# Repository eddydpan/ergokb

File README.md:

# ergokb
A custom ergo keyboard, fully designed by myself

## design
I had always taken pride in my typing speed. I felt like I can comfortably navigate a computer with the keyboard, and I have been recently growing these skills with KDE Plasma as my DE and vim as my text editor. I had the realization that if I continue typing for the rest of my life, I'd want to make sure I take care of my hands. 

Therefore, I started looking into more ergonomic keyboards. There are plenty of off-the-shelf models--the Sofle, Aurora Corne, and Iris all looked like good options. However, I am a stickler when it comes to price--the absolute worst outcome for me would be buying an expensive off-the-shelf keyboard and it not being a good-fit for my hands that lie on the smaller side. In truth, these keyboards were difficult to vet. With some more research, I came across the [Caldera](https://github.com/christianselig/caldera-keyboard), an open-source keyboard build made by a hobbyist on [YouTube](https://www.youtube.com/watch?v=7UXsD7nSfDY). Aside from the clickbait video title, it was an insightful watch, and it got me interested in learning PCB design. With the price and uncertainties of an off-the-shelf keyboard, I figured I'd rather design my own and put my engineering degree to good use. 

## layout iteration pipeline

In order to test the keyboard geometry custom to my hands, I used Claude Code to build out a pipline to print out the left and right half of the design specified in `ergogen/config.yaml`. After 8 iterations, I landed on a 6-column Colstag split-keyboard with a 4-key thumb cluster. I had to play around with the orientation to ensure everything fits within my reach. This will allow me to map a QWERTY layout as a backup to trying out a more modern and ergonomic layout such as [Gallium](https://layouts.wiki/layouts/2023/gallium/#gallium-colstag).

### pipeline setup guide

```sh
npm --prefix scripts install   # once: ergogen 4.1.0 + pdfkit, pinned (Node tooling lives in scripts/)
```

1. **Edit** `ergogen/config.yaml`. The stagger, splay, and rotation knobs are in its `units:` block.
2. **Visualize**: paste it into [ergogen.xyz](https://ergogen.xyz), or run `npm --prefix scripts run build` for DXFs and the KiCad boards in `output/ergogen/`.
3. **Print sheet**: `npm --prefix scripts run pdf` writes `output/print/ergokb-layout.pdf` (page 1 = left half, page 2 = right, 1:1 scale).
   - Legends come from `keymap.yaml`. Finger rows are written in desk order, left to right; thumbs are keyed by role (`home`, `curl`, `palm`, `extra`).
   - `npm --prefix scripts run pdf -- --layers gallium,qwerty,nav`: the first layer gets the big legend and the others go in the corners (up to 4 layers).
   - `npm --prefix scripts run pdf -- --set ring_stagger=0.5cy --out try.pdf` overrides a tuning knob for one print.
   - `npm --prefix scripts run pdf -- --paper a4`
4. **Print** at 100% / "Actual size" (not "Fit to page"). Check that the 100 mm bar measures 100 mm, then cut along the dashed line.
   The footer records the git commit and every tuning value, so you can tell old prints apart.

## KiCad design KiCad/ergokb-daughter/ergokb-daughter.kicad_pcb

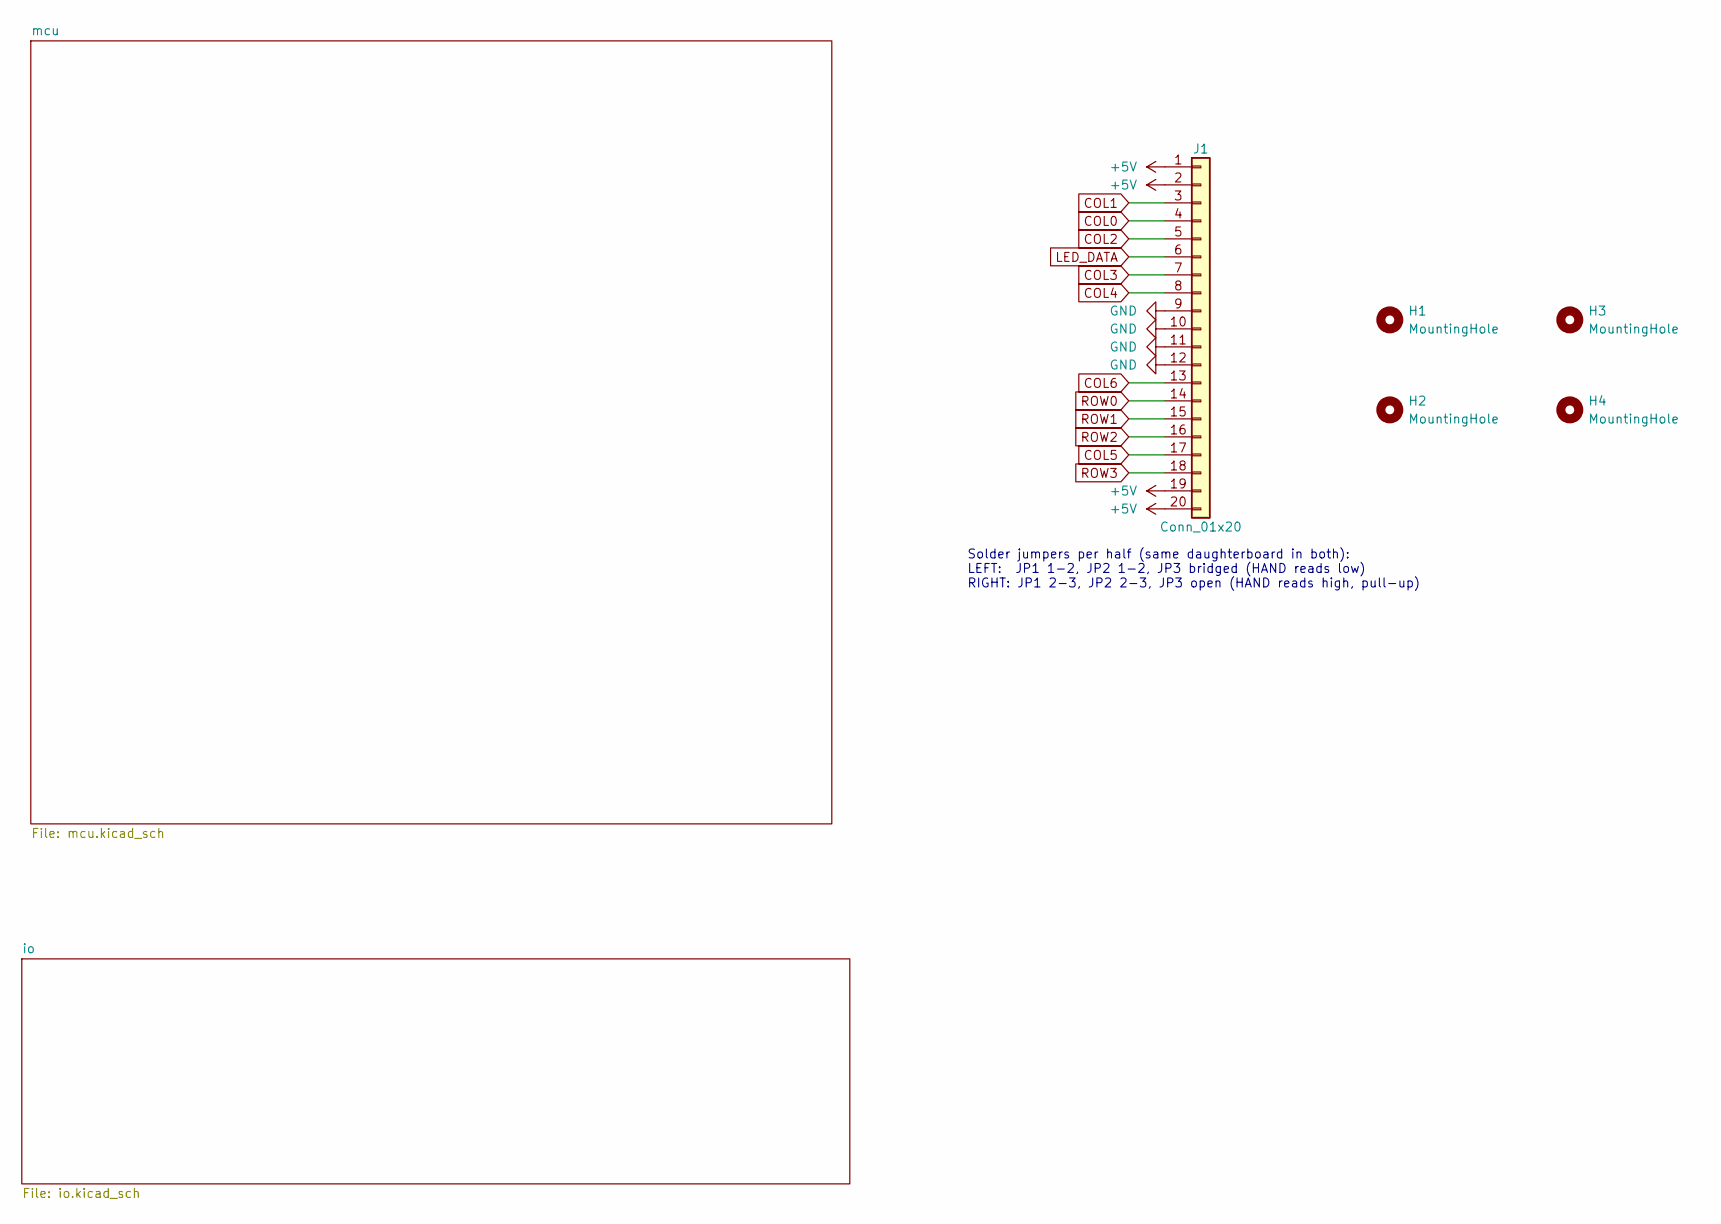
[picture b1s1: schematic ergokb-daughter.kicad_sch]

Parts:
H1, H2, H3, H4: MountingHole; MountingHole_2.2mm_M2
J1: Conn_01x20; PinHeader_1x20_P1.27mm_Vertical

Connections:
+5V: J1.1, J1.2, J1.19, J1.20; also elsewhere on the board
COL0: J1.4; also elsewhere on the board
COL1: J1.3; also elsewhere on the board
COL2: J1.5; also elsewhere on the board
COL3: J1.7; also elsewhere on the board
COL4: J1.8; also elsewhere on the board
COL5: J1.17; also elsewhere on the board
COL6: J1.13; also elsewhere on the board
GND: J1.9, J1.10, J1.11, J1.12; also elsewhere on the board
LED_DATA: J1.6; also elsewhere on the board
ROW0: J1.14; also elsewhere on the board
ROW1: J1.15; also elsewhere on the board
ROW2: J1.16; also elsewhere on the board
ROW3: J1.18; also elsewhere on the board

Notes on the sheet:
Solder jumpers per half (same daughterboard in both): LEFT: JP1 1-2, JP2 1-2, JP3 bridged (HAND reads low) RIGHT: JP1 2-3, JP2 2-3, JP3 open (HAND reads high, pull-up)

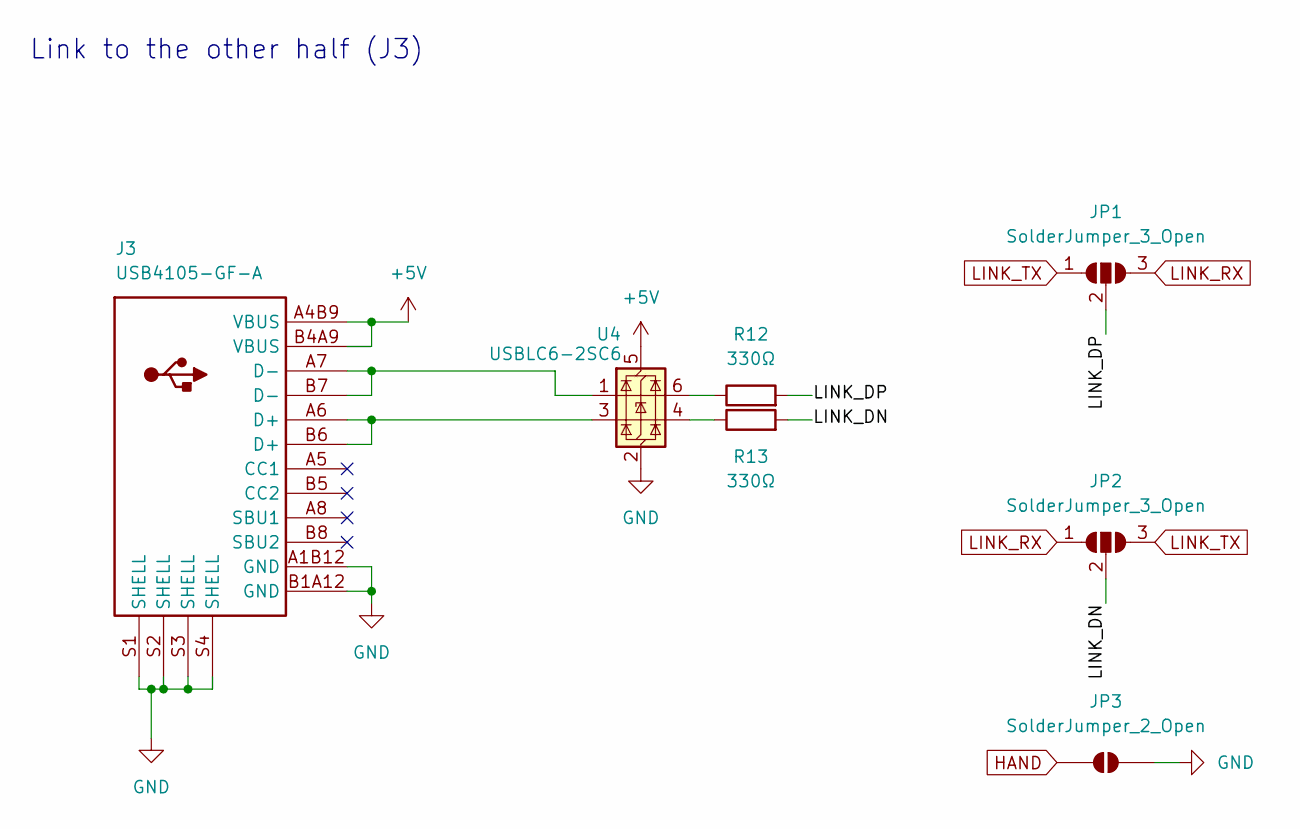
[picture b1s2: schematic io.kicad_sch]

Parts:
J3: USB4105-GF-A
JP1, JP2: SolderJumper_3_Open; SolderJumper-3_P1.3mm_Open_RoundedPad1.0x1.5mm_NumberLabels
JP3: SolderJumper_2_Open; SolderJumper-2_P1.3mm_Open_RoundedPad1.0x1.5mm
R12, R13: 330Ω; R_0603_1608Metric
U4: USBLC6-2SC6; SOT-23-6

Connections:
+5V: J3.A4B9 (VBUS), J3.B4A9 (VBUS), U4.5 (VBUS); also elsewhere on the board
/io/LINK_DN: JP2.2 (C), R13.2
/io/LINK_DP: JP1.2 (C), R12.2
GND: J3.A1B12 (GND), J3.B1A12 (GND), J3.S1 (SHELL), J3.S2 (SHELL), J3.S3 (SHELL), J3.S4 (SHELL), JP3.2 (B), U4.2 (GND); also elsewhere on the board
HAND: JP3.1 (A); also elsewhere on the board
LINK_RX: JP1.3 (B), JP2.1 (A); also elsewhere on the board
LINK_TX: JP1.1 (A), JP2.3 (B); also elsewhere on the board
unnamed: J3.A6 (D+), J3.B6 (D+), U4.3 (I/O2)
unnamed: J3.A7 (D-), J3.B7 (D-), U4.1 (I/O1)
unnamed: R12.1, U4.6 (I/O1)
unnamed: R13.1, U4.4 (I/O2)

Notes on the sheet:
Link to the other half (J3)

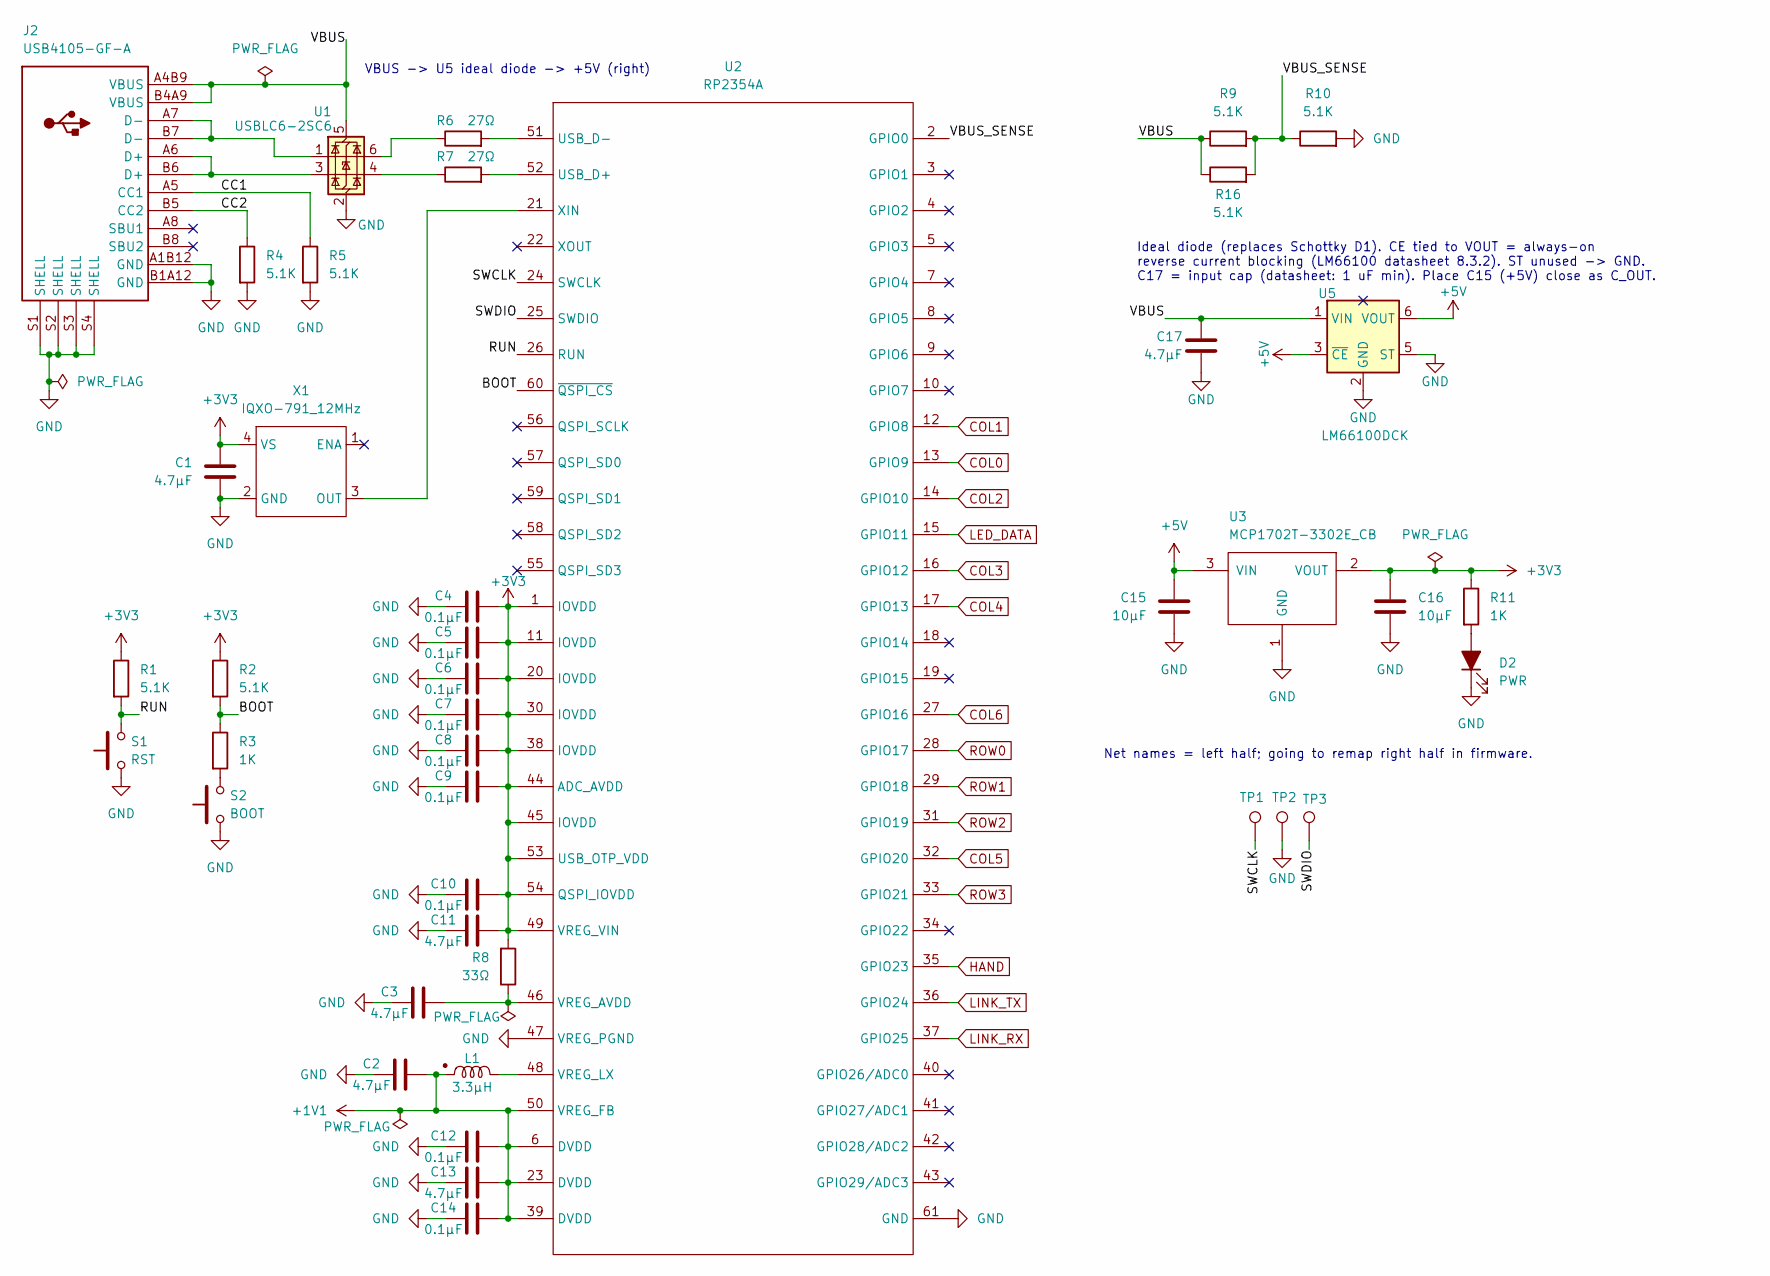
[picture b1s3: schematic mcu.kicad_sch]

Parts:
C1, C13: 4.7µF; C_0402_1005Metric
C2, C11: 4.7µF; R_0402_1005Metric
C3, C17: 4.7µF; C_0603_1608Metric
C4, C5, C12: 0.1µF; C_0603_1608Metric
C6, C7, C8, C9, C10, C14: 0.1µF; C_0402_1005Metric
C15, C16: 10µF; C_0603_1608Metric
D2: PWR; LED_0805_2012Metric
J2: USB4105-GF-A
L1: 3.3µH; AOTA-B201610S3R3-101-T
R1, R2, R9, R10, R16: 5.1K; R_0603_1608Metric
R3: 1K; R_0603_1608Metric
R4, R5: 5.1K; R_0402_1005Metric
R6, R7: 27Ω; R_0402_1005Metric
R8: 33Ω; R_0402_1005Metric
R11: 1K; R_0402_1005Metric
S1: RST; SW_SPST_B3U-1000P
S2: BOOT; SW_SPST_B3U-1000P
TP1, TP2, TP3: TestPoint; TestPoint_Pad_D1.0mm
U1: USBLC6-2SC6; SOT-23-6
U2: RP2354A; RP2350A_QFN-60_EP_7.75x7.75_Pitch0.4mm
U3: MCP1702T-3302E_CB; SOT-23-3
U5: LM66100DCK; SOT-363_SC-70-6
X1: IQXO-791_12MHz; IQXO-791

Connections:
+1V1: C2.2, C12.2, C13.2, C14.2, L1.1, U2.6 (DVDD), U2.23 (DVDD), U2.39 (DVDD), U2.50 (VREG_FB)
+3V3: C1.2, C4.2, C5.2, C6.2, C7.2, C8.2, C9.2, C10.2, C11.2, C16.1, R1.1, R2.1, R8.2, R11.1, U2.1 (IOVDD), U2.11 (IOVDD), U2.20 (IOVDD), U2.30 (IOVDD), U2.38 (IOVDD), U2.44 (ADC_AVDD), U2.45 (IOVDD), U2.49 (VREG_VIN), U2.53 (USB_OTP_VDD), U2.54 (QSPI_IOVDD), U3.2 (VOUT), X1.4 (VS)
+5V: C15.2, U3.3 (VIN), U5.3 (~CE), U5.6 (VOUT); also elsewhere on the board
/mcu/BOOT: R2.2, R3.1, U2.60 (~QSPI_CS)
/mcu/CC1: J2.A5 (CC1), R5.1
/mcu/CC2: J2.B5 (CC2), R4.1
/mcu/RUN: R1.2, S1.2, U2.26 (RUN)
/mcu/SWCLK: TP1.1 (1_1), U2.24 (SWCLK)
/mcu/SWDIO: TP3.1 (1_1), U2.25 (SWDIO)
/mcu/VBUS: C17.1, J2.A4B9 (VBUS), J2.B4A9 (VBUS), R9.1, R16.1, U1.5 (VBUS), U5.1 (VIN)
/mcu/VBUS_SENSE: R9.2, R10.1, R16.2, U2.2 (GPIO0)
COL0: U2.13 (GPIO9); also elsewhere on the board
COL1: U2.12 (GPIO8); also elsewhere on the board
COL2: U2.14 (GPIO10); also elsewhere on the board
COL3: U2.16 (GPIO12); also elsewhere on the board
COL4: U2.17 (GPIO13); also elsewhere on the board
COL5: U2.32 (GPIO20); also elsewhere on the board
COL6: U2.27 (GPIO16); also elsewhere on the board
GND: C1.1, C2.1, C3.1, C4.1, C5.1, C6.1, C7.1, C8.1, C9.1, C10.1, C11.1, C12.1, C13.1, C14.1, C15.1, C16.2, C17.2, D2.1 (K), J2.A1B12 (GND), J2.B1A12 (GND), J2.S1 (SHELL), J2.S2 (SHELL), J2.S3 (SHELL), J2.S4 (SHELL), R4.2, R5.2, R10.2, S1.1, S2.1, TP2.1 (1_1), U1.2 (GND), U2.47 (VREG_PGND), U2.61 (GND), U3.1 (GND), U5.2 (GND), U5.5 (ST), X1.2 (GND); also elsewhere on the board
HAND: U2.35 (GPIO23); also elsewhere on the board
LED_DATA: U2.15 (GPIO11); also elsewhere on the board
LINK_RX: U2.37 (GPIO25); also elsewhere on the board
LINK_TX: U2.36 (GPIO24); also elsewhere on the board
unnamed: D2.2 (A), R11.2
unnamed: J2.A6 (D+), J2.B6 (D+), U1.3 (I/O2)
unnamed: J2.A7 (D-), J2.B7 (D-), U1.1 (I/O1)
unnamed: R3.2, S2.2
unnamed: R6.1, U1.6 (I/O1)
unnamed: R7.1, U1.4 (I/O2)
unnamed: R7.2, U2.52 (USB_D+)
unnamed: R6.2, U2.51 (USB_D-)
unnamed: C3.2, R8.1, U2.46 (VREG_AVDD)
unnamed: L1.2, U2.48 (VREG_LX)
unnamed: U2.21 (XIN), X1.3 (OUT)
ROW0: U2.28 (GPIO17); also elsewhere on the board
ROW1: U2.29 (GPIO18); also elsewhere on the board
ROW2: U2.31 (GPIO19); also elsewhere on the board
ROW3: U2.33 (GPIO21); also elsewhere on the board

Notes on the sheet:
Ideal diode (replaces Schottky D1). CE tied to VOUT = always-on reverse current blocking (LM66100 datasheet 8.3.2). ST unused -> GND. C17 = input cap (datasheet: 1 uF min). Place C15 (+5V) close as C_OUT.
VBUS -> U5 ideal diode -> +5V (right)
Net names = left half; going to remap right half in firmware.

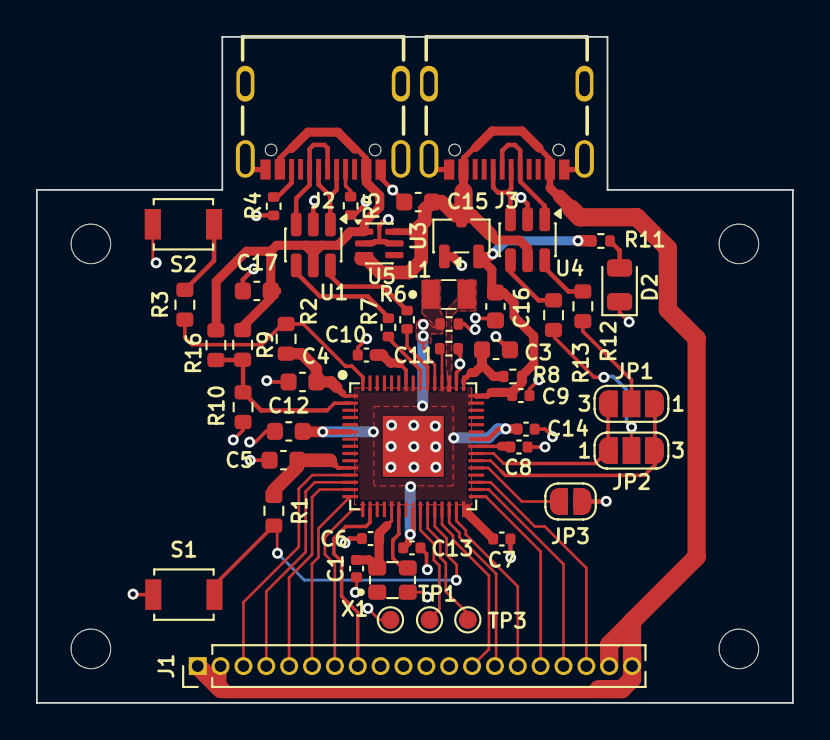
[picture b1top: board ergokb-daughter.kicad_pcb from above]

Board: 2 copper layers, 42.0 x 37.0 mm, 54 parts (0 on the bottom side), 44 nets.

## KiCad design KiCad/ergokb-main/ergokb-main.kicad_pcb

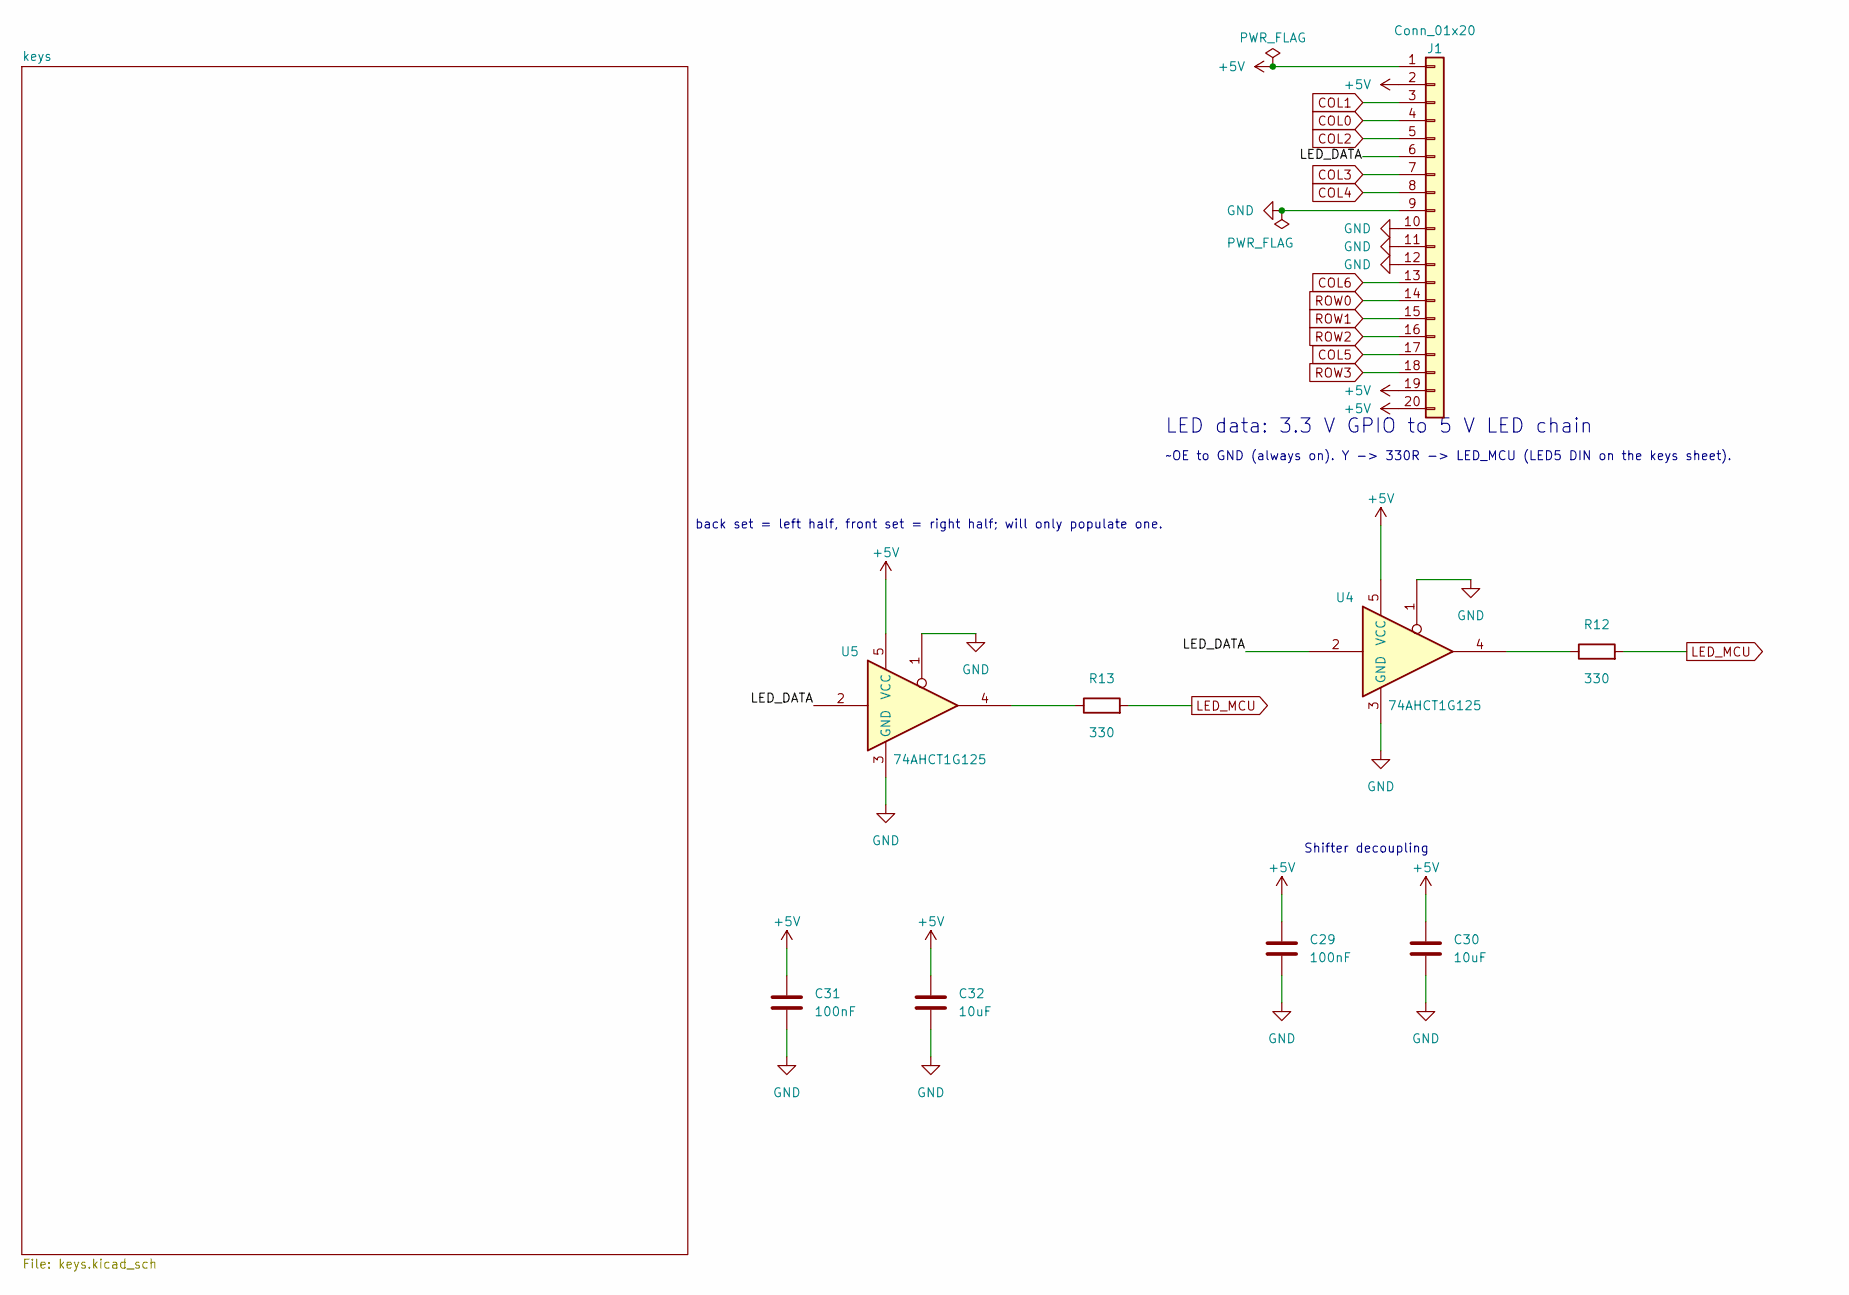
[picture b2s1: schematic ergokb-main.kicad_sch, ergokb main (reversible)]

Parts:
C29, C31: 100nF; C_0603_1608Metric
C30, C32: 10uF; C_0603_1608Metric
J1: Conn_01x20; PinHeader_1x20_P1.27mm_Vertical
R12, R13: 330; R_0603_1608Metric
U4, U5: 74AHCT1G125; SOT-23-5

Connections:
+5V: C29.1, C30.1, C31.1, C32.1, J1.1, J1.2, J1.19, J1.20, U4.5 (VCC), U5.5 (VCC); also elsewhere on the board
/LED_DATA: J1.6, U4.2, U5.2
COL0: J1.4; also elsewhere on the board
COL1: J1.3; also elsewhere on the board
COL2: J1.5; also elsewhere on the board
COL3: J1.7; also elsewhere on the board
COL4: J1.8; also elsewhere on the board
COL5: J1.17; also elsewhere on the board
COL6: J1.13; also elsewhere on the board
GND: C29.2, C30.2, C31.2, C32.2, J1.9, J1.10, J1.11, J1.12, U4.1, U4.3 (GND), U5.1, U5.3 (GND); also elsewhere on the board
LED_MCU: R12.2, R13.2; also elsewhere on the board
unnamed: R12.1, U4.4
unnamed: R13.1, U5.4
ROW0: J1.14; also elsewhere on the board
ROW1: J1.15; also elsewhere on the board
ROW2: J1.16; also elsewhere on the board
ROW3: J1.18; also elsewhere on the board

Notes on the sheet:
back set = left half, front set = right half; will only populate one.
Shifter decoupling
LED data: 3.3 V GPIO to 5 V LED chain
~OE to GND (always on). Y -> 330R -> LED_MCU (LED5 DIN on the keys sheet).

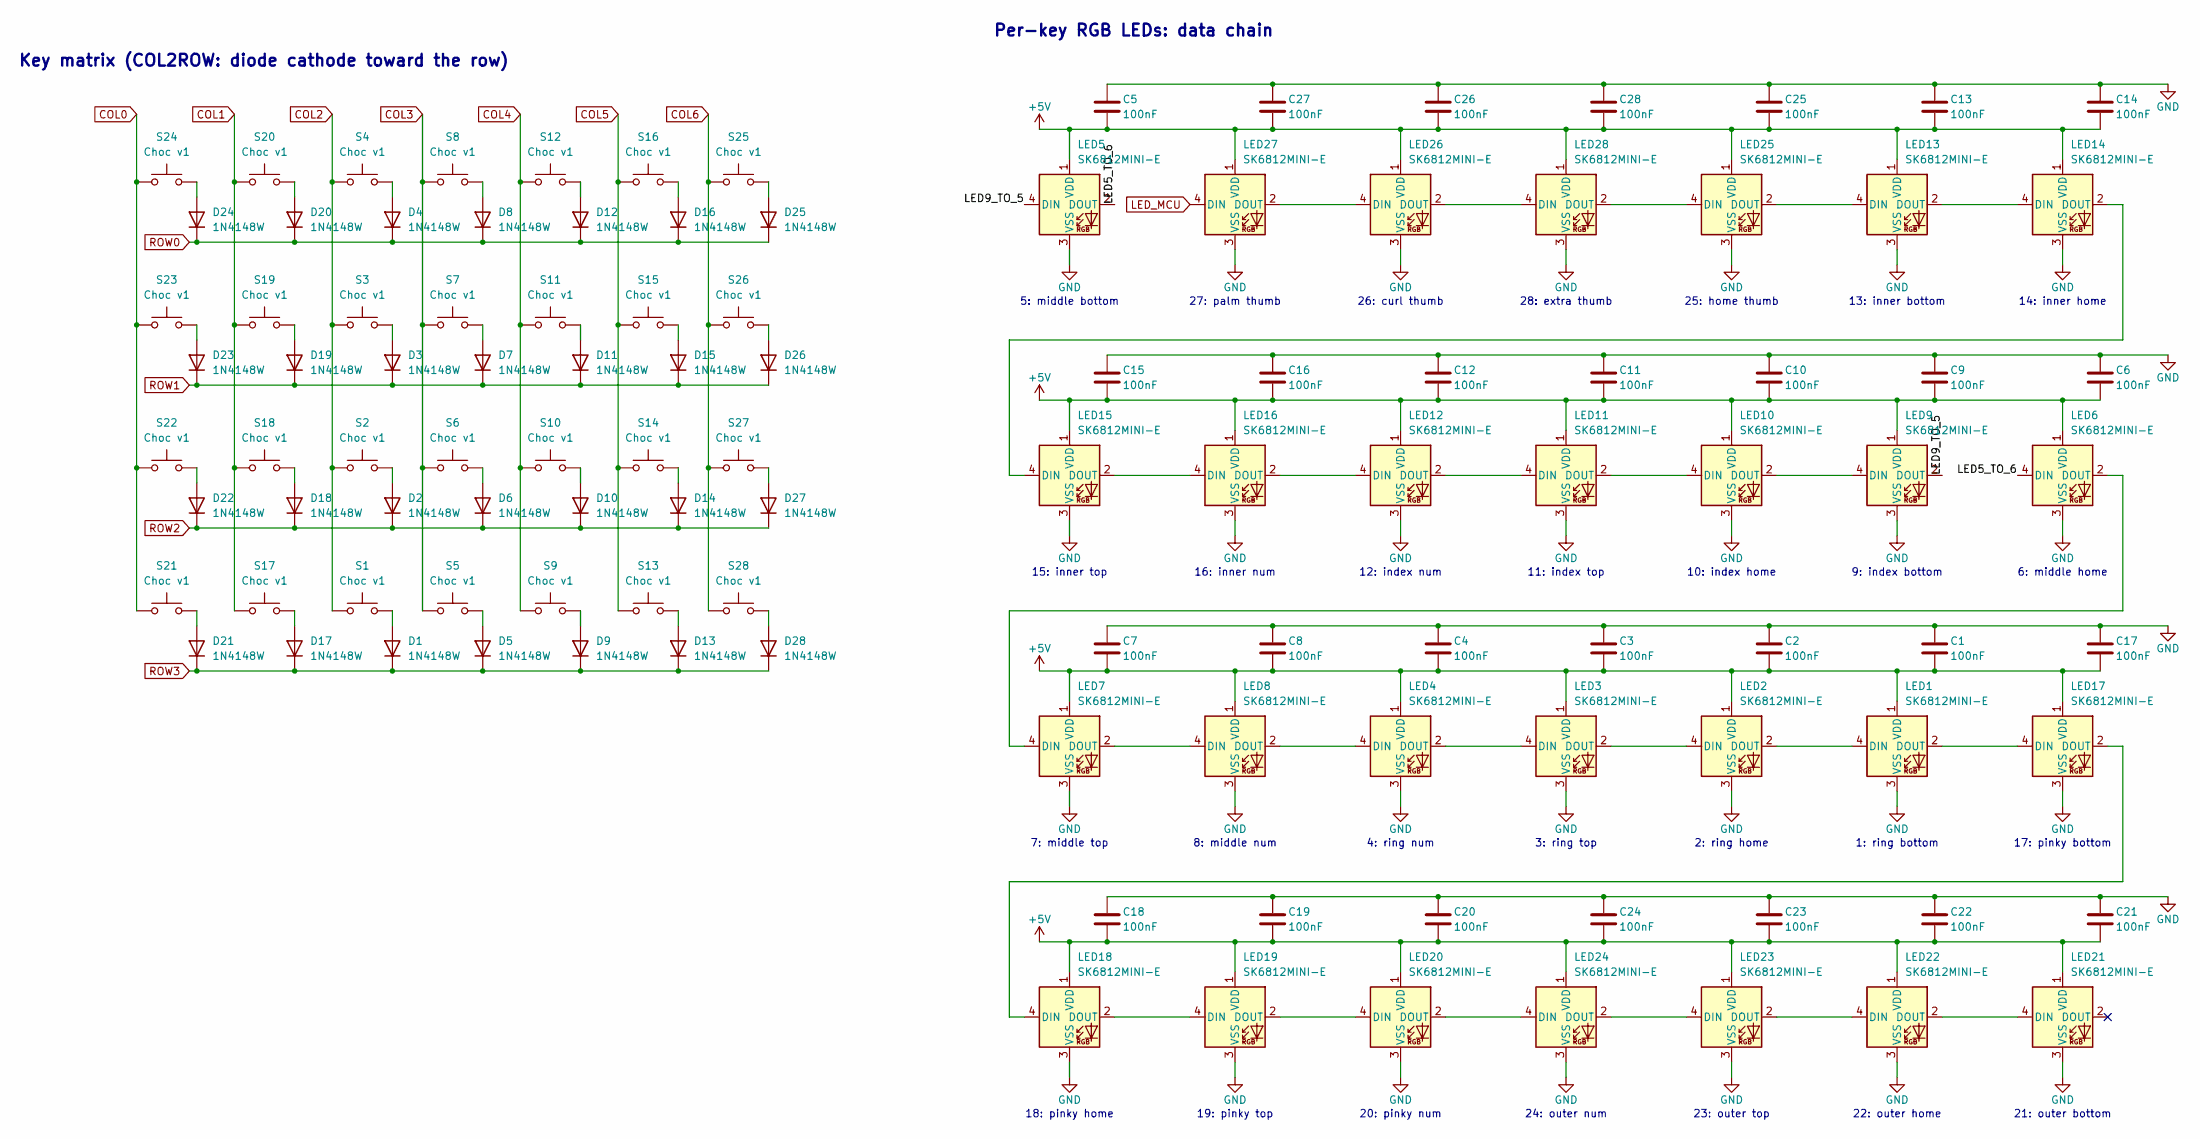
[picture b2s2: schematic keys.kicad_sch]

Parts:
C1, C2, C3, C4, C5, C6, C7, C8, C9, C10, C11, C12, C13, C14, C15, C16, C17, C18, C19, C20, C21, C22, C23, C24, C25, C26, C27, C28: 100nF; C_0603_mirrored
D1, D2, D3, D4, D5, D6, D7, D8, D9, D10, D11, D12, D13, D14, D15, D16, D17, D18, D19, D20, D21, D22, D23, D24, D25, D26, D27, D28: 1N4148W; D_SOD-123_mirrored
LED1, LED2, LED3, LED4, LED5, LED6, LED7, LED8, LED9, LED10, LED11, LED12, LED13, LED14, LED15, LED16, LED17, LED18, LED19, LED20, LED21, LED22, LED23, LED24, LED25, LED26, LED27, LED28: SK6812MINI-E; led_SK6812mini-e (per-key, reversible)
S1, S2, S3, S4, S5, S6, S7, S8, S9, S10, S11, S12, S13, S14, S15, S16, S17, S18, S19, S20, S21, S22, S23, S24, S25, S26, S27, S28: Choc v1; switch_choc_v1_v2

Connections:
+5V: C1.1, C2.1, C3.1, C4.1, C5.1, C6.1, C7.1, C8.1, C9.1, C10.1, C11.1, C12.1, C13.1, C14.1, C15.1, C16.1, C17.1, C18.1, C19.1, C20.1, C21.1, C22.1, C23.1, C24.1, C25.1, C26.1, C27.1, C28.1, LED1.1 (VDD), LED2.1 (VDD), LED3.1 (VDD), LED4.1 (VDD), LED5.1 (VDD), LED6.1 (VDD), LED7.1 (VDD), LED8.1 (VDD), LED9.1 (VDD), LED10.1 (VDD), LED11.1 (VDD), LED12.1 (VDD), LED13.1 (VDD), LED14.1 (VDD), LED15.1 (VDD), LED16.1 (VDD), LED17.1 (VDD), LED18.1 (VDD), LED19.1 (VDD), LED20.1 (VDD), LED21.1 (VDD), LED22.1 (VDD), LED23.1 (VDD), LED24.1 (VDD), LED25.1 (VDD), LED26.1 (VDD), LED27.1 (VDD), LED28.1 (VDD); also elsewhere on the board
/keys/LED5_TO_6: LED5.2 (DOUT), LED6.4 (DIN)
/keys/LED9_TO_5: LED5.4 (DIN), LED9.2 (DOUT)
COL0: S21.1, S22.1, S23.1, S24.1; also elsewhere on the board
COL1: S17.1, S18.1, S19.1, S20.1; also elsewhere on the board
COL2: S1.1, S2.1, S3.1, S4.1; also elsewhere on the board
COL3: S5.1, S6.1, S7.1, S8.1; also elsewhere on the board
COL4: S9.1, S10.1, S11.1, S12.1; also elsewhere on the board
COL5: S13.1, S14.1, S15.1, S16.1; also elsewhere on the board
COL6: S25.1, S26.1, S27.1, S28.1; also elsewhere on the board
GND: C1.2, C2.2, C3.2, C4.2, C5.2, C6.2, C7.2, C8.2, C9.2, C10.2, C11.2, C12.2, C13.2, C14.2, C15.2, C16.2, C17.2, C18.2, C19.2, C20.2, C21.2, C22.2, C23.2, C24.2, C25.2, C26.2, C27.2, C28.2, LED1.3 (VSS), LED2.3 (VSS), LED3.3 (VSS), LED4.3 (VSS), LED5.3 (VSS), LED6.3 (VSS), LED7.3 (VSS), LED8.3 (VSS), LED9.3 (VSS), LED10.3 (VSS), LED11.3 (VSS), LED12.3 (VSS), LED13.3 (VSS), LED14.3 (VSS), LED15.3 (VSS), LED16.3 (VSS), LED17.3 (VSS), LED18.3 (VSS), LED19.3 (VSS), LED20.3 (VSS), LED21.3 (VSS), LED22.3 (VSS), LED23.3 (VSS), LED24.3 (VSS), LED25.3 (VSS), LED26.3 (VSS), LED27.3 (VSS), LED28.3 (VSS); also elsewhere on the board
LED_MCU: LED27.4 (DIN); also elsewhere on the board
unnamed: D1.2 (A), S1.2
unnamed: D2.2 (A), S2.2
unnamed: D3.2 (A), S3.2
unnamed: D4.2 (A), S4.2
unnamed: D5.2 (A), S5.2
unnamed: D6.2 (A), S6.2
unnamed: D7.2 (A), S7.2
unnamed: D8.2 (A), S8.2
unnamed: D9.2 (A), S9.2
unnamed: D10.2 (A), S10.2
unnamed: D11.2 (A), S11.2
unnamed: D12.2 (A), S12.2
unnamed: D13.2 (A), S13.2
unnamed: D14.2 (A), S14.2
unnamed: D15.2 (A), S15.2
unnamed: D16.2 (A), S16.2
unnamed: D17.2 (A), S17.2
unnamed: D18.2 (A), S18.2
unnamed: D19.2 (A), S19.2
unnamed: D20.2 (A), S20.2
unnamed: D21.2 (A), S21.2
unnamed: D22.2 (A), S22.2
unnamed: D23.2 (A), S23.2
unnamed: D24.2 (A), S24.2
unnamed: D25.2 (A), S25.2
unnamed: D26.2 (A), S26.2
unnamed: D27.2 (A), S27.2
unnamed: D28.2 (A), S28.2
unnamed: LED1.4 (DIN), LED2.2 (DOUT)
unnamed: LED1.2 (DOUT), LED17.4 (DIN)
unnamed: LED2.4 (DIN), LED3.2 (DOUT)
unnamed: LED3.4 (DIN), LED4.2 (DOUT)
unnamed: LED4.4 (DIN), LED8.2 (DOUT)
unnamed: LED6.2 (DOUT), LED7.4 (DIN)
unnamed: LED7.2 (DOUT), LED8.4 (DIN)
unnamed: LED10.4 (DIN), LED11.2 (DOUT)
unnamed: LED9.4 (DIN), LED10.2 (DOUT)
unnamed: LED11.4 (DIN), LED12.2 (DOUT)
unnamed: LED12.4 (DIN), LED16.2 (DOUT)
unnamed: LED13.4 (DIN), LED25.2 (DOUT)
unnamed: LED13.2 (DOUT), LED14.4 (DIN)
unnamed: LED14.2 (DOUT), LED15.4 (DIN)
unnamed: LED15.2 (DOUT), LED16.4 (DIN)
unnamed: LED17.2 (DOUT), LED18.4 (DIN)
unnamed: LED18.2 (DOUT), LED19.4 (DIN)
unnamed: LED19.2 (DOUT), LED20.4 (DIN)
unnamed: LED20.2 (DOUT), LED24.4 (DIN)
unnamed: LED21.4 (DIN), LED22.2 (DOUT)
unnamed: LED22.4 (DIN), LED23.2 (DOUT)
unnamed: LED23.4 (DIN), LED24.2 (DOUT)
unnamed: LED25.4 (DIN), LED28.2 (DOUT)
unnamed: LED26.4 (DIN), LED27.2 (DOUT)
unnamed: LED26.2 (DOUT), LED28.4 (DIN)
ROW0: D4.1 (K), D8.1 (K), D12.1 (K), D16.1 (K), D20.1 (K), D24.1 (K), D25.1 (K); also elsewhere on the board
ROW1: D3.1 (K), D7.1 (K), D11.1 (K), D15.1 (K), D19.1 (K), D23.1 (K), D26.1 (K); also elsewhere on the board
ROW2: D2.1 (K), D6.1 (K), D10.1 (K), D14.1 (K), D18.1 (K), D22.1 (K), D27.1 (K); also elsewhere on the board
ROW3: D1.1 (K), D5.1 (K), D9.1 (K), D13.1 (K), D17.1 (K), D21.1 (K), D28.1 (K); also elsewhere on the board

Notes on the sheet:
24: outer num
4: ring num
27: palm thumb
21: outer bottom
Per-key RGB LEDs: data chain
17: pinky bottom
11: index top
22: outer home
2: ring home
25: home thumb
16: inner num
19: pinky top
26: curl thumb
10: index home
14: inner home
1: ring bottom
8: middle num
Key matrix (COL2ROW: diode cathode toward the row)
23: outer top
6: middle home
7: middle top
13: inner bottom
18: pinky home
5: middle bottom
28: extra thumb
12: index num
20: pinky num
15: inner top
3: ring top
9: index bottom

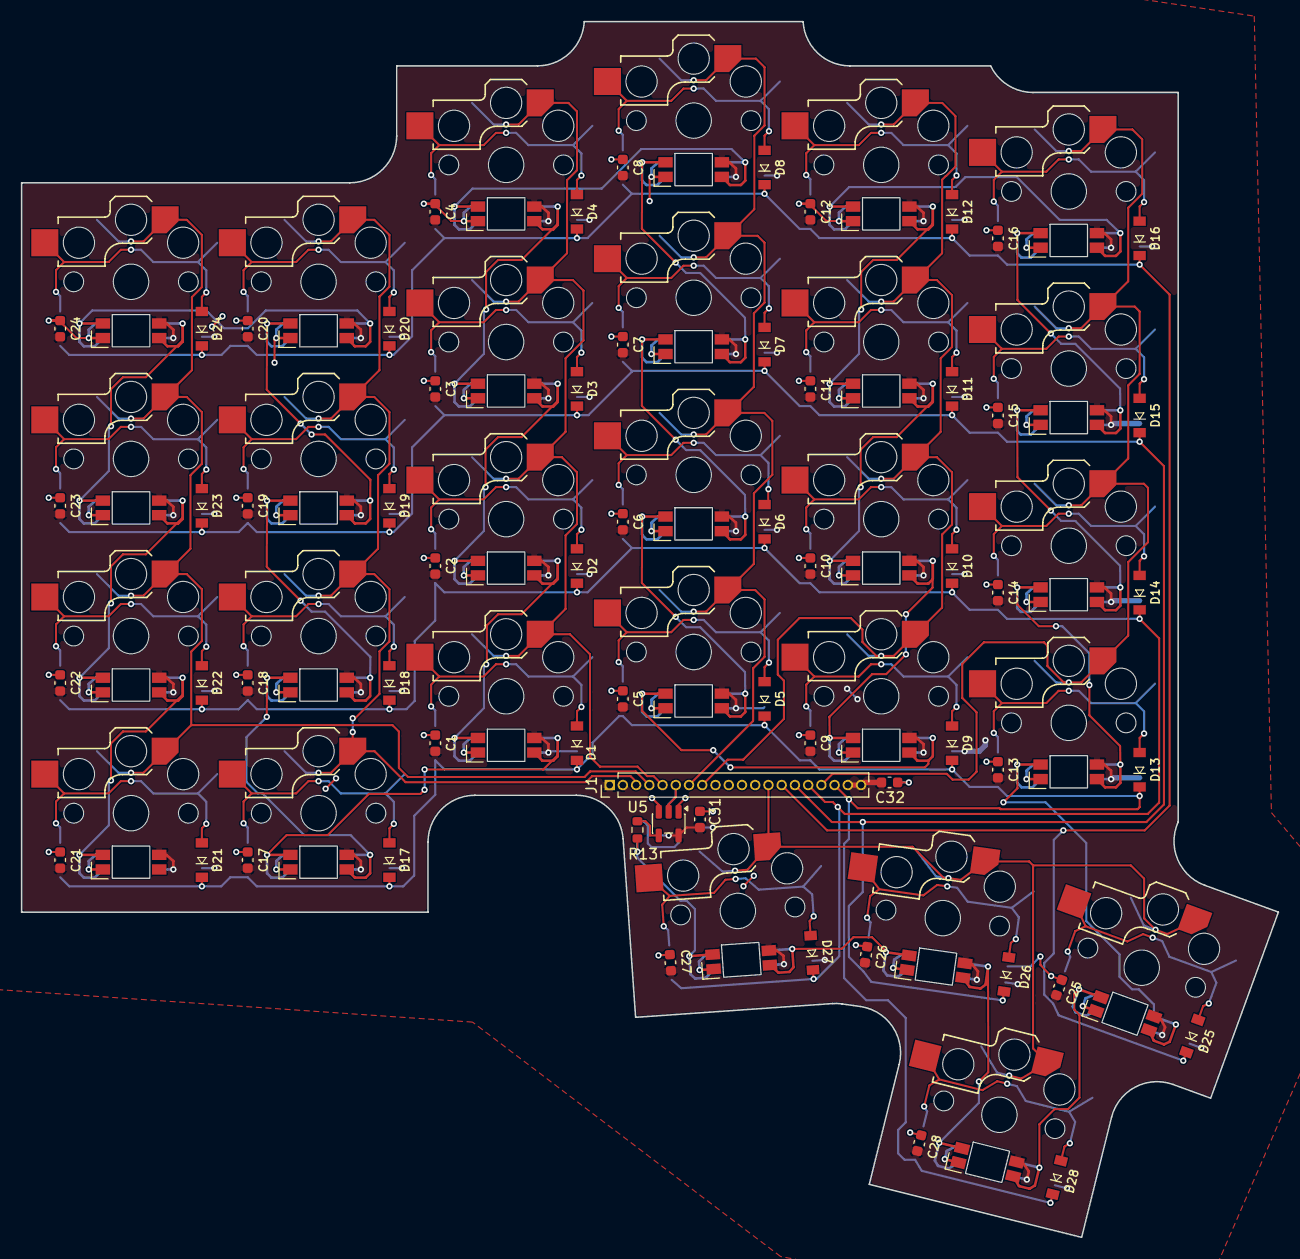
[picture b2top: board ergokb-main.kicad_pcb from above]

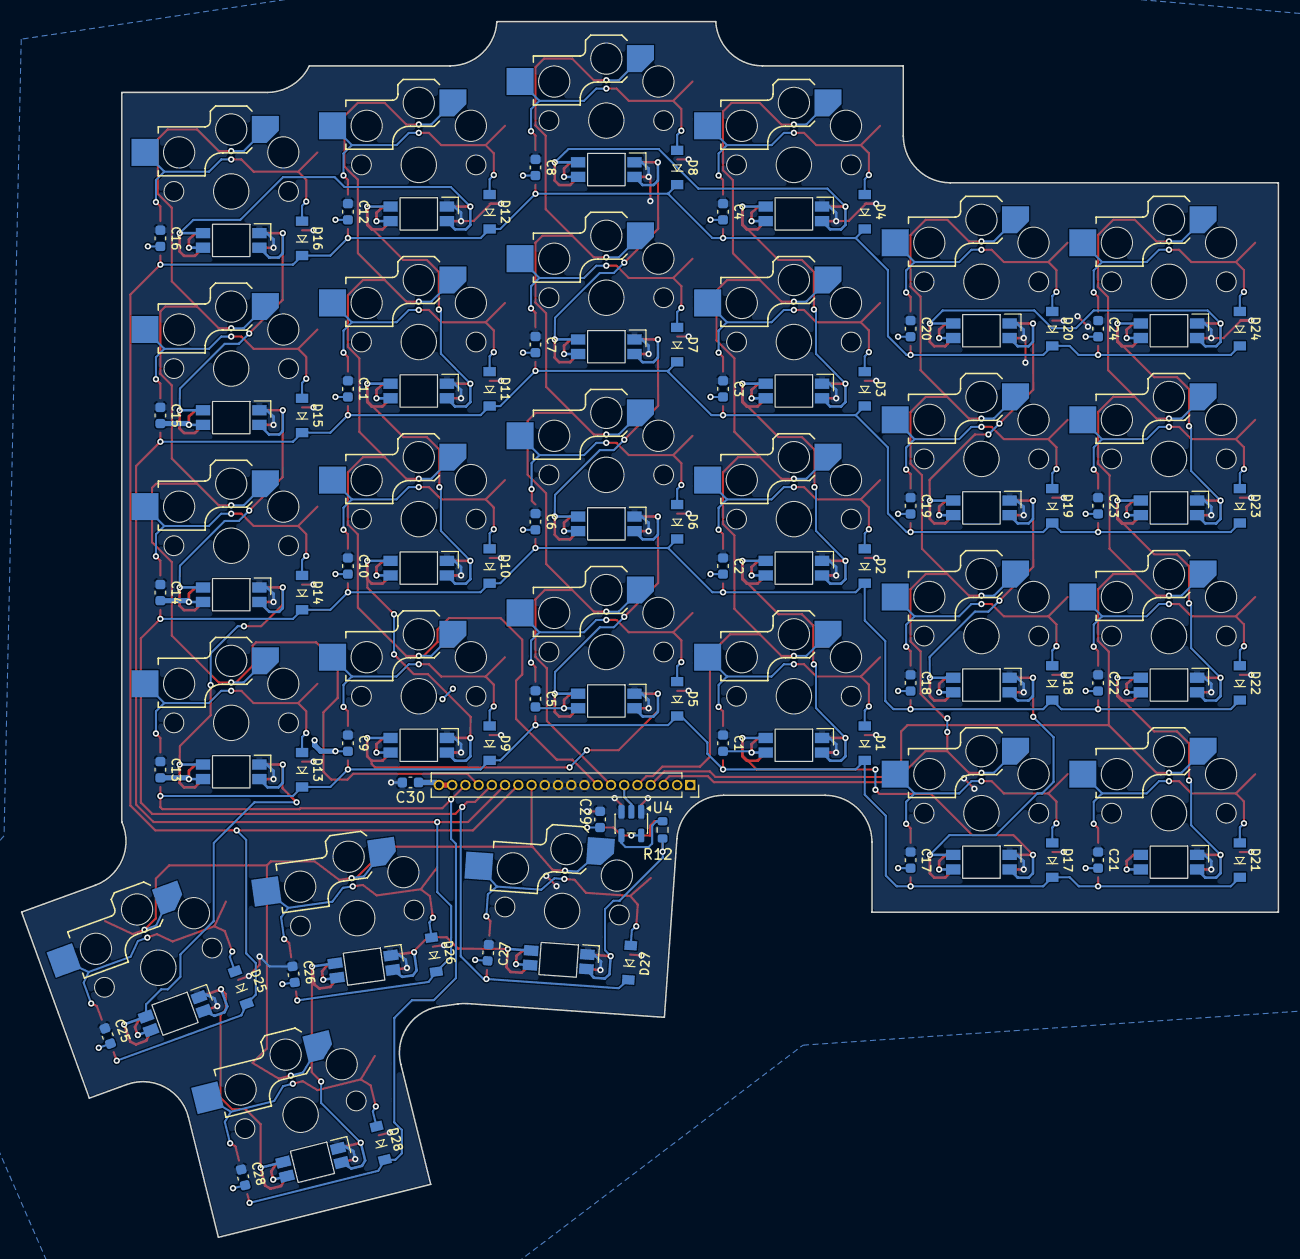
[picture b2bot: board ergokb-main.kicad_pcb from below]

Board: 2 copper layers, 120.6 x 116.7 mm, 121 parts (116 on the bottom side), 72 nets.
